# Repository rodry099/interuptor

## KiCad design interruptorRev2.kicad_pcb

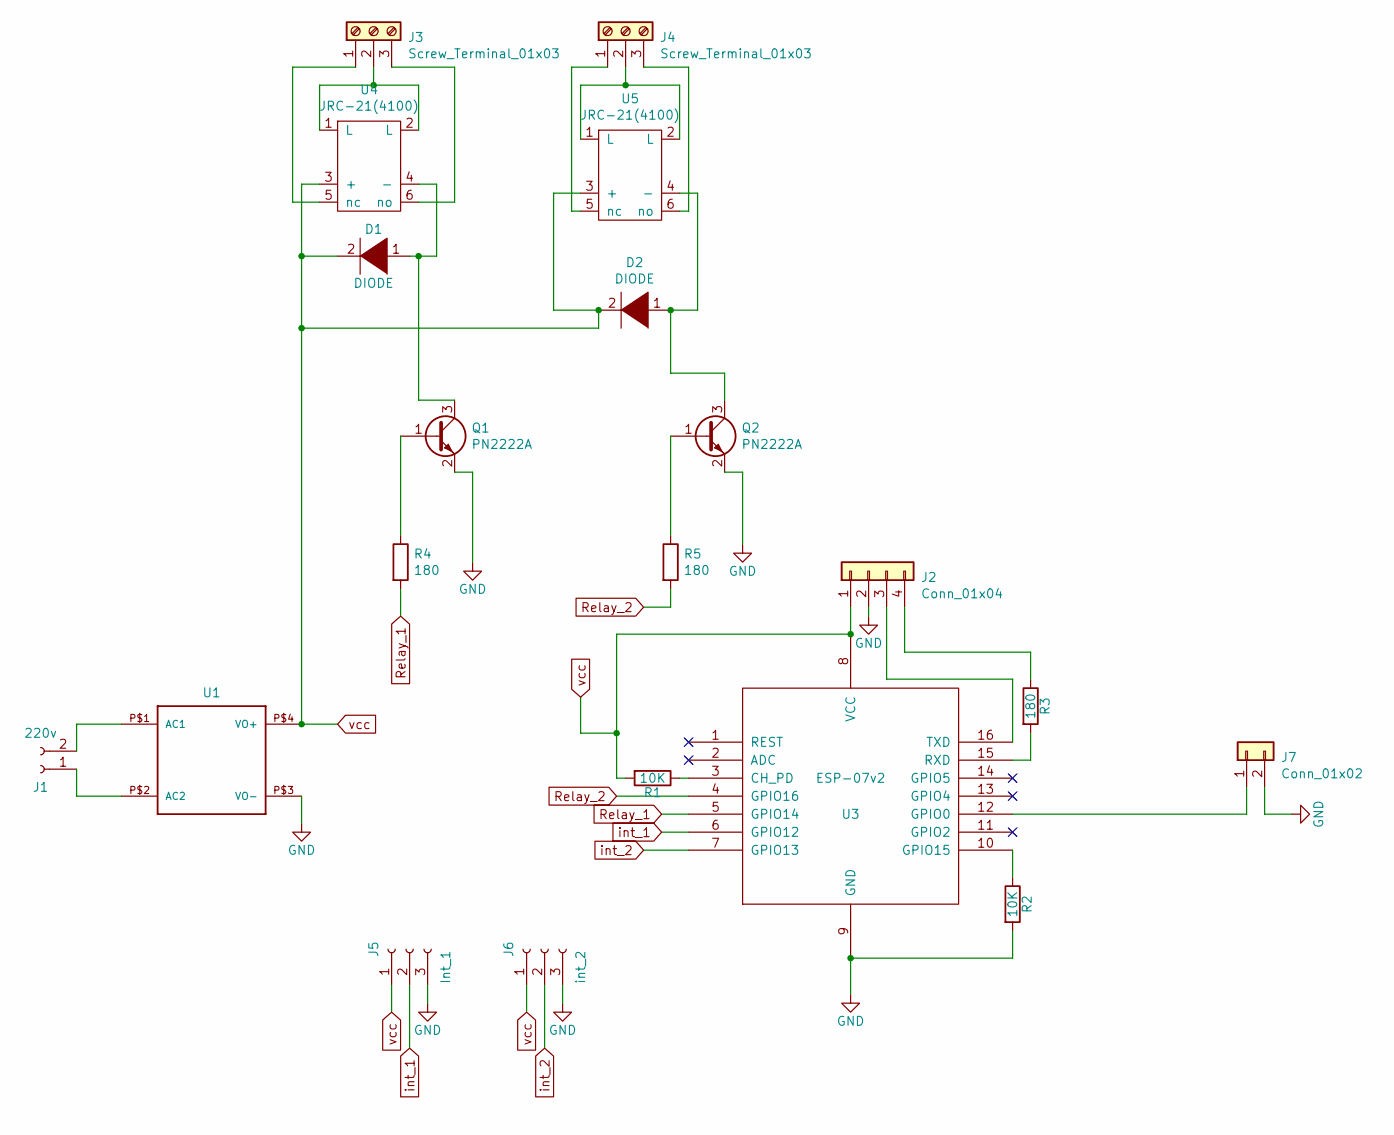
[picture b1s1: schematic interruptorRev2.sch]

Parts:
D1, D2: DIODE; D_1206_3216Metric_Pad1.42x1.75mm_HandSolder
J1: 220v; TerminalBlock_bornier-2_P5.08mm
J2: Conn_01x04; PinHeader_1x04_P2.54mm_Vertical
J3, J4: Screw_Terminal_01x03; TerminalBlock_bornier-3_P5.08mm
J5: Int_1; PinHeader_1x03_P2.54mm_Vertical
J6: int_2; PinHeader_1x03_P2.54mm_Vertical
J7: Conn_01x02; PinHeader_1x02_P2.54mm_Vertical
Q1, Q2: PN2222A; SOT-23
R1, R2: 10K; R_1206_3216Metric_Pad1.42x1.75mm_HandSolder
R3, R4, R5: 180; R_1206_3216Metric_Pad1.42x1.75mm_HandSolder
U1: HLK-PM01
U3: ESP-07v2
U4, U5: JRC-21(4100); JRC-21F

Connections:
GND: J2.2, J5.3, J6.3, J7.2, Q1.2 (E), Q2.2 (E), R2.2, U1.P$3 (VO-), U3.9 (GND)
unnamed: D1.1 (K), Q1.3 (C), U4.4 (-)
unnamed: D2.1 (K), Q2.3 (C), U5.4 (-)
unnamed: J1.1, U1.P$2 (AC2)
unnamed: J1.2, U1.P$1 (AC1)
unnamed: J2.3, U3.16 (TXD)
unnamed: J2.4, R3.1
unnamed: J3.1, U4.5 (nc)
unnamed: J3.2, U4.1 (L), U4.2 (L)
unnamed: J3.3, U4.6 (no)
unnamed: J4.1, U5.5 (nc)
unnamed: J4.2, U5.1 (L), U5.2 (L)
unnamed: J4.3, U5.6 (no)
unnamed: J7.1, U3.12 (GPIO0)
unnamed: Q1.1 (B), R4.1
unnamed: Q2.1 (B), R5.1
unnamed: R1.1, U3.3 (CH_PD)
unnamed: R2.1, U3.10 (GPIO15)
unnamed: R3.2, U3.15 (RXD)
Relay_1: R4.2, U3.5 (GPIO14)
Relay_2: R5.2, U3.4 (GPIO16)
int_1: J5.2, U3.6 (GPIO12)
int_2: J6.2, U3.7 (GPIO13)
vcc: D1.2 (A), D2.2 (A), J2.1, J5.1, J6.1, R1.2, U1.P$4 (VO+), U3.8 (VCC), U4.3 (+), U5.3 (+)

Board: 2 copper layers, 20 parts (9 on the bottom side), 24 nets, no tracks yet.

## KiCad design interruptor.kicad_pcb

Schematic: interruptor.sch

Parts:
C1, C2: 10uF; C_1206_3216Metric_Pad1.42x1.75mm_HandSolder
D1, D2: DIODE; D_DO-35_SOD27_P7.62mm_Horizontal
J1: 220v; TerminalBlock_bornier-2_P5.08mm
J2: tx/rx; PinHeader_1x03_P2.54mm_Vertical
J3, J4: Screw_Terminal_01x03; TerminalBlock_bornier-3_P5.08mm
J5: Int_1; PinHeader_1x03_P2.54mm_Vertical
J6: int_2; PinHeader_1x03_P2.54mm_Vertical
J7: switch; PinHeader_1x03_P2.54mm_Vertical
K1, K2: SRD-05VDC-SL-C; RELAY_SRD-05VDC-SL-C
Q1, Q2: PN2222A; TO-92_Inline
R1, R2: 10K; R_1206_3216Metric_Pad1.42x1.75mm_HandSolder
R3, R4, R5: 180; R_1206_3216Metric_Pad1.42x1.75mm_HandSolder
U1: HLK-PM01
U2: LM1117-3.3; SOT-223
U3: ESP-07v2

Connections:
GND: C1.2, C2.2, J2.3, J5.3, J6.3, J7.3, Q1.1, Q2.1, R2.2, U1.P$3 (VO-), U2.1, U3.9
unnamed: C1.1, D1.2 (A), D2.2 (A), K1.A1, K2.A1, U1.P$4 (VO+), U2.3
unnamed: D1.1 (K), K1.A2, Q1.3
unnamed: D2.1 (K), K2.A2, Q2.3
unnamed: J1.1, U1.P$2 (AC2)
unnamed: J1.2, U1.P$1 (AC1)
unnamed: J2.1, U3.16
unnamed: J2.2, R3.1
unnamed: J3.1, K1.NO
unnamed: J3.2, K1.COM
unnamed: J3.3, K1.NC
unnamed: J4.1, K2.NO
unnamed: J4.2, K2.COM
unnamed: J4.3, K2.NC
unnamed: J7.2, U3.12
unnamed: Q1.2, R4.1
unnamed: Q2.2, R5.1
unnamed: R1.1, U3.3
unnamed: R2.1, U3.10
unnamed: R3.2, U3.15
Relay_1: R4.2, U3.5
Relay_2: R5.2, U3.4
int_1: J5.2, U3.6
int_2: J6.2, U3.7
vcc: C2.1, J5.1, J6.1, R1.2, U2.2, U3.8

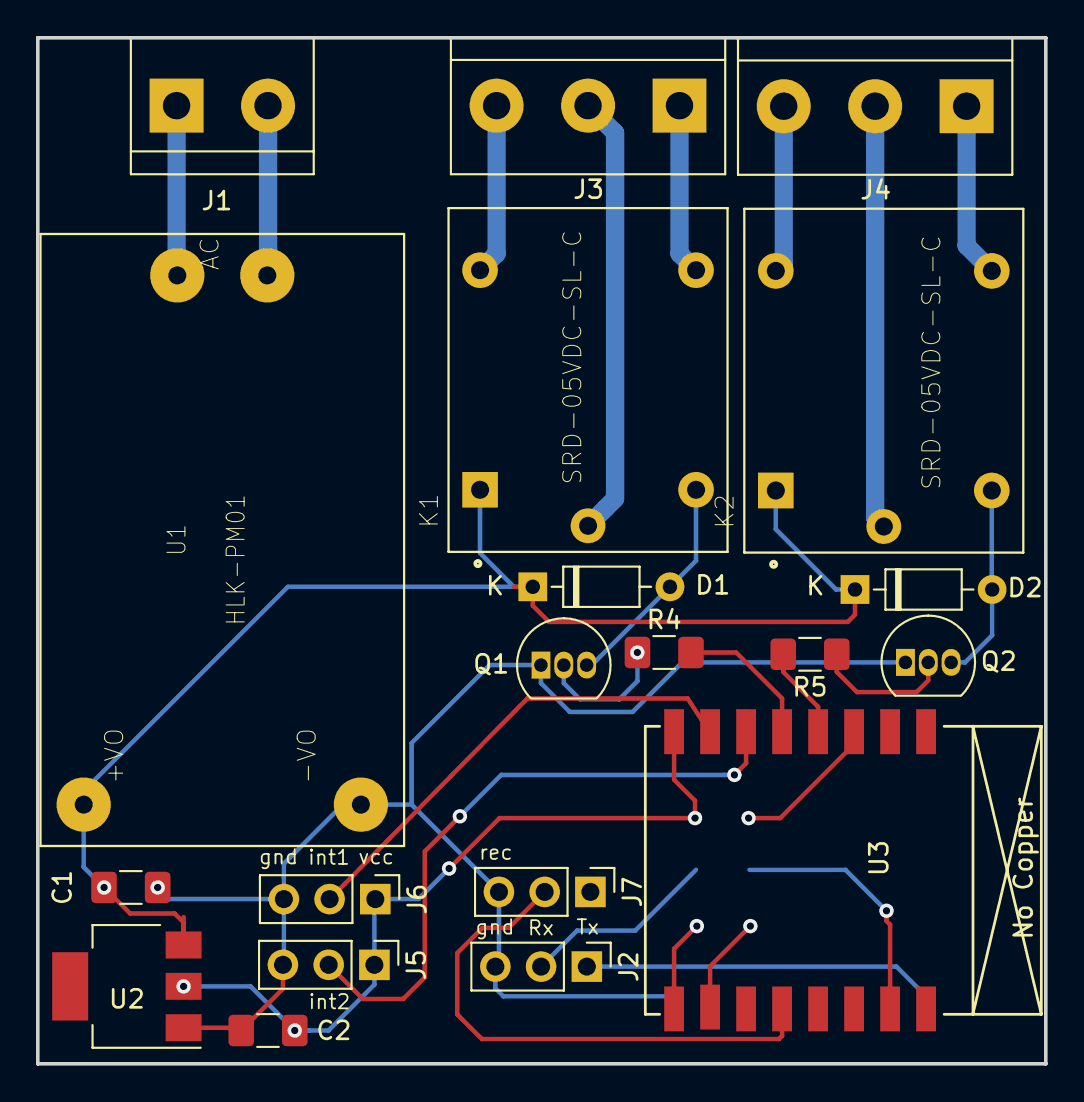
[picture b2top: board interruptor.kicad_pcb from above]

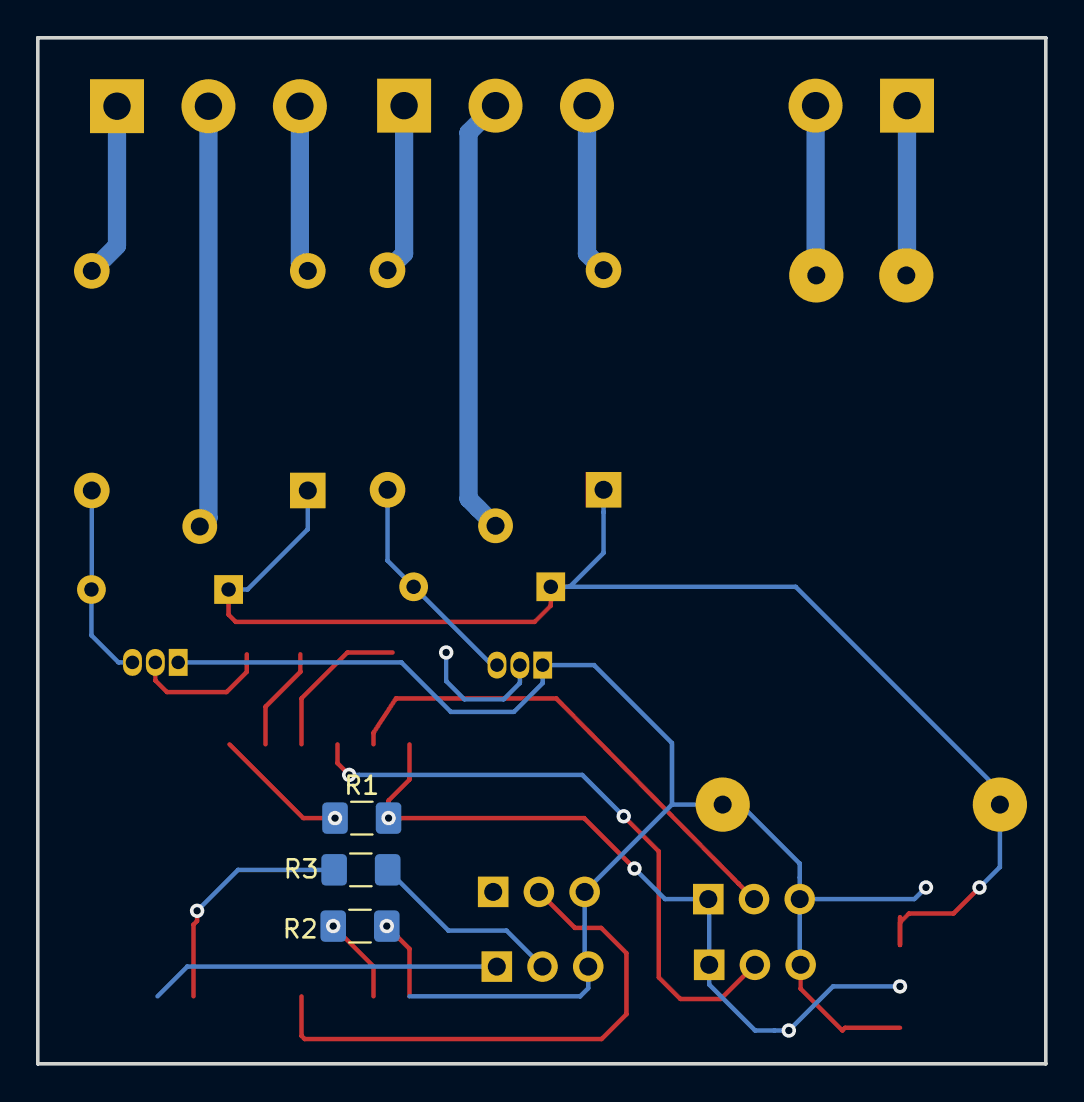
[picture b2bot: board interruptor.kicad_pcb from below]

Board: 2 copper layers, 56.0 x 57.0 mm, 23 parts (3 on the bottom side), 25 nets.

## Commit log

2019-05-16 primera revision de proyecto
2019-05-16 colocacion componentes en pcb y conexionado
2019-05-18 pistas dibujadas
2019-05-18 modificadas pistas smd
2019-05-18 modificadas pistas smd 2
2019-08-14 intentando reducir tamanyo
2019-08-15 nueva version con librerias
2019-08-15 pines para flashear
2019-08-15 lib rev
2019-08-15 no gerbers
2019-08-15 ignore gerbers
2019-08-19 lectura corriente primer esbozo
2019-08-21 esquema dividido por secciones
2019-08-21 relays en esquema separado
2019-08-21 regulador voltaje 3v3
